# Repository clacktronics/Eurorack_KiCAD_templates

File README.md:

# Eurorack_KiCAD_templates
 Simple templates for starting a modular project. Mix and match parts into a folder for your new project. Each board is a seperate KiCAD project including the front panel.

 ## Connector panels
  For horizontal PCB modules (when the PCB surface is parallel with the front panel) this board holds all the connectors, but could also contain the main circuit if it fits.

  For vertical boards (board surface 90 degrees to front panel) there is no connector panel just main board.

  boards are 106mm high and 1mm smaller in width from the front panel to allow easy fitting next to other modules. In the `Dwgs.user` layer there are dimensions and the outline of the front panel for reference.

  There is a 100mm height version to take advantage of the cheaper PCB pooling 100x100mm limit that many fab houses use.

 ## Front panels
 They are is layed out according to [Doepfer standards](https://www.doepfer.de/a100_man/a100m_e.htm) 128.5mm high and "actual module width" in the table. They have elogated holes for easy adjustment left and right on the rack. 

 ## Main boards
 For horizontal PCB modules this board is at the back with a 10 pin Eurorack connector already drawn out in the schematic.

 For vertical boards

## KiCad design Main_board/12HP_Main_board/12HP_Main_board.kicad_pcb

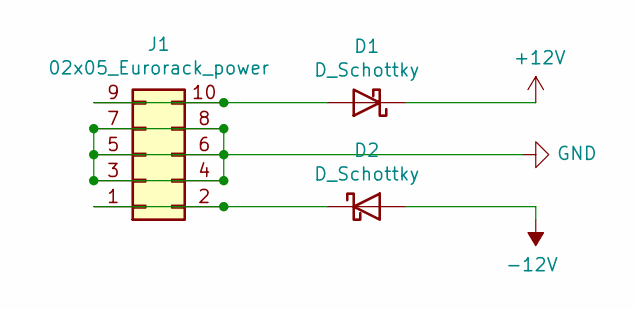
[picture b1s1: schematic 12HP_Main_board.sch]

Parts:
D1, D2: D_Schottky; D_SMA
J1: 02x05_Eurorack_power; IDC-Header_2x05_P2.54mm_Vertical

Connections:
+12V: D1.1 (K)
-12V: D2.2 (A)
GND: J1.3, J1.4, J1.5, J1.6, J1.7, J1.8
unnamed: D1.2 (A), J1.9, J1.10
unnamed: D2.1 (K), J1.1, J1.2

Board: 2 copper layers, 3 parts (0 on the bottom side), 3 nets, no tracks yet.

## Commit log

2021-10-13 Update .gitignore
    Ignore *.sch-bak
2021-10-13 Update .gitignore
    fp-info-cache ignore
2021-10-13 Initial boards WIP
2021-10-13 Started readme
2021-10-13 Added all images
2021-10-13 Moved images for clarity
